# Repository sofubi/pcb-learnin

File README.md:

A repo made to follow along with Ai03's pcb guide

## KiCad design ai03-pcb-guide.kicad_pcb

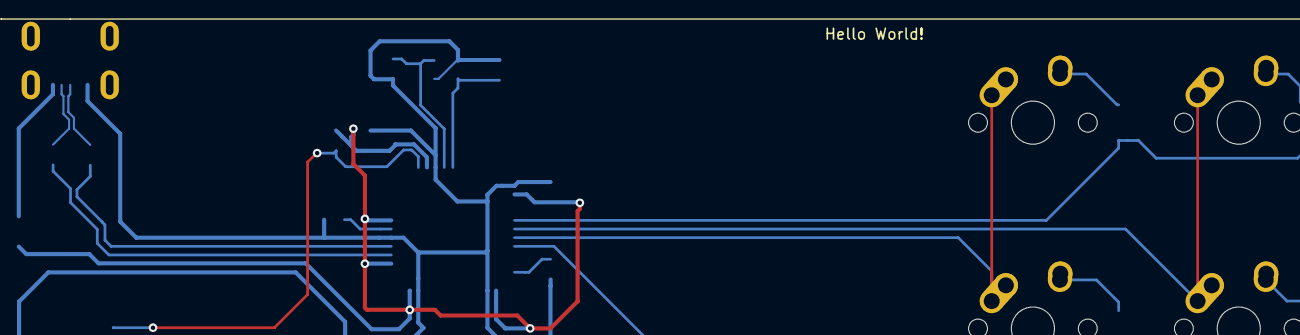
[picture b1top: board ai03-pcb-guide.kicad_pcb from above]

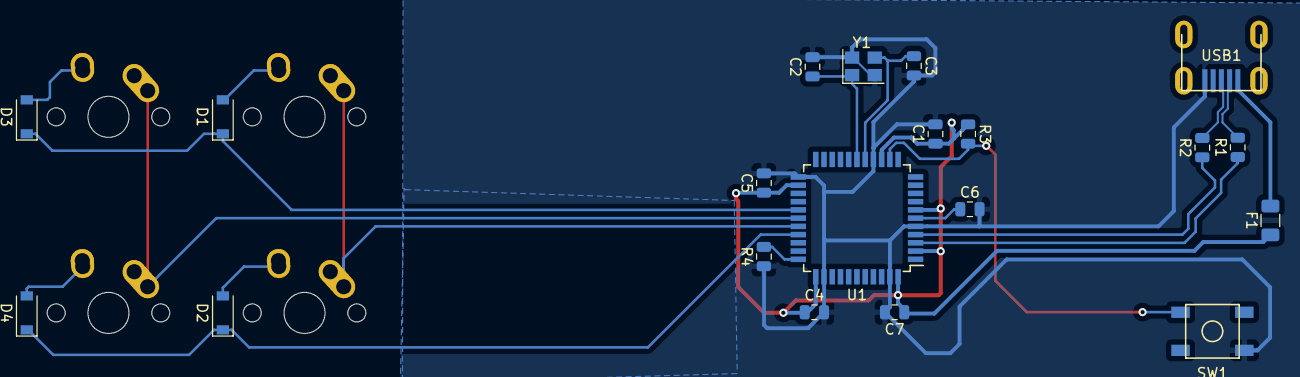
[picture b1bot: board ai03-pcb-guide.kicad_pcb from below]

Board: 2 copper layers, 24 parts (20 on the bottom side), 20 nets.

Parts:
C1, C4, C5: 0.1uF; C_0805_2012Metric
C2, C3: 22pF; C_0805_2012Metric
C6: 1uF; C_0805_2012Metric
C7: 10uF; C_0805_2012Metric
D1, D2, D3, D4: SOD_123; D_SOD-123
F1: 500mA; Fuse_1206_3216Metric
MX1, MX2, MX3, MX4: MX-NoLED; MX-1U-NoLED
R1, R2: 22; R_0805_2012Metric
R3, R4: 10k; R_0805_2012Metric
SW1: SW_Push; SKQG-1155865
U1: ATmega32U4-AU; TQFP-44_10x10mm_P0.8mm
USB1: Molex-0548190589
Y1: Crystal_GND24_Small; Crystal_SMD_3225-4Pin_3.2x2.5mm

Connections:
+5V: C1.1, C4.1, C5.1, C7.1, F1.1, R3.1, U1.2, U1.7, U1.14, U1.24, U1.34, U1.44
COL0: MX1.1, MX2.1, U1.29
COL1: MX3.1, MX4.1, U1.28
D+: R2.2, USB1.3
D-: R1.2, USB1.4
GND: C1.2, C2.2, C3.2, C4.2, C5.2, C6.2, C7.2, R4.1, SW1.1, U1.5, U1.15, U1.23, U1.35, U1.43, USB1.1, Y1.2, Y1.4
unnamed: C2.1, U1.17, Y1.1
unnamed: C3.1, U1.16, Y1.3
unnamed: C6.1, U1.6
unnamed: D1.2, MX1.2
unnamed: D2.2, MX2.2
unnamed: D3.2, MX3.2
unnamed: D4.2, MX4.2
unnamed: R1.1, U1.3
unnamed: R2.1, U1.4
unnamed: R3.2, SW1.2, U1.13
unnamed: R4.2, U1.33
ROW0: D1.1, D3.1, U1.27
ROW1: D2.1, D4.1, U1.30
VCC: F1.2, USB1.5

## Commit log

2020-08-15 initial
2020-08-15 Creates kicad project
2020-08-15 Adds footprint libraries for keyboard specific needs
2020-08-15 Sets up footprint libraries
2020-08-15 Half of the schematic done, saving work
2020-08-15 Schematic complete
2020-08-15 Applies footprints from schematic
2020-08-15 Completes routing
2020-08-15 Completes pcb creation
